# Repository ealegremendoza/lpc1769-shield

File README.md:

# PRYECTOR LPC1769-SHIELD
- La idea del mismo es poder conectarse rápidamente al lpcxpresso lpc1769.
- Proyecto creado en KICAD4.

### Todo listo para el planchado. 
- Ver en la carpeta pdf el archivo listo para planchar.

Alegre Ezequiel.

https://github.com/ealegremendoza

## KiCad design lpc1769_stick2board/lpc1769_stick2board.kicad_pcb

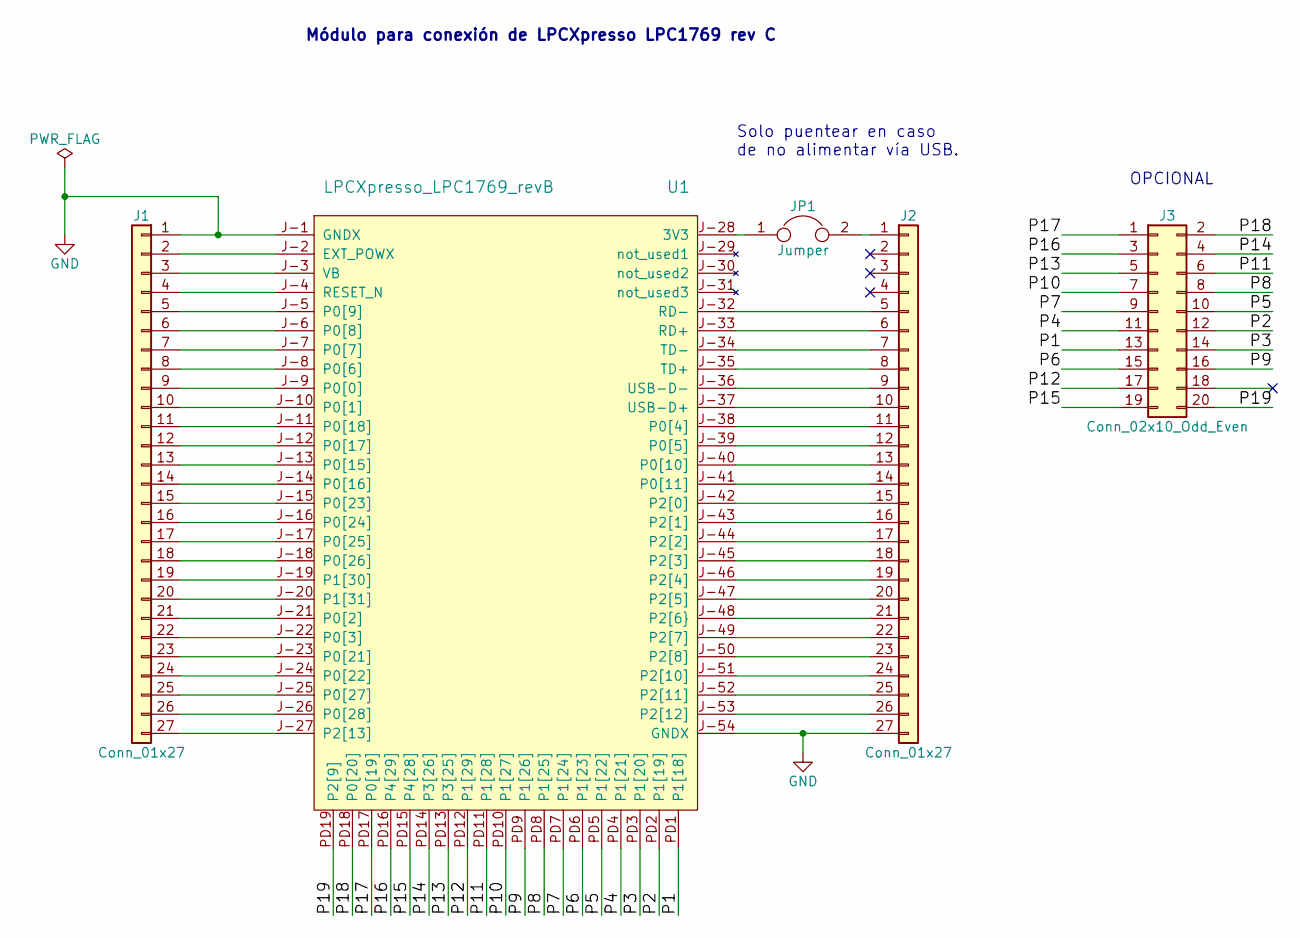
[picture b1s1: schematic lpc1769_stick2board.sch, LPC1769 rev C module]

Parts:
J1, J2: Conn_01x27; Socket_Strip_Straight_1x27_Pitch2.54mm
J3: Conn_02x10_Odd_Even; Socket_Strip_Straight_2x10_Pitch2.54mm
JP1: Jumper; Socket_Strip_Straight_1x02_Pitch2.54mm
U1: LPCXpresso_LPC1769_revB; lpc1769_board_revC

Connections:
/P1: J3.13, U1.PD1 (P1[18])
/P2: J3.12, U1.PD2 (P1[19])
/P3: J3.14, U1.PD3 (P1[20])
/P4: J3.11, U1.PD4 (P1[21])
/P5: J3.10, U1.PD5 (P1[22])
/P6: J3.15, U1.PD6 (P1[23])
/P7: J3.9, U1.PD7 (P1[24])
/P8: J3.8, U1.PD8 (P1[25])
/P9: J3.16, U1.PD9 (P1[26])
/P10: J3.7, U1.PD10 (P1[27])
/P11: J3.6, U1.PD11 (P1[28])
/P12: J3.17, U1.PD12 (P1[29])
/P13: J3.5, U1.PD13 (P3[25])
/P14: J3.4, U1.PD14 (P3[26])
/P15: J3.19, U1.PD15 (P4[28])
/P16: J3.3, U1.PD16 (P4[29])
/P17: J3.1, U1.PD17 (P0[19])
/P18: J3.2, U1.PD18 (P0[20])
/P19: J3.20, U1.PD19 (P2[9])
GND: J1.1, J2.27, U1.J-1 (GNDX), U1.J-54 (GNDX)
unnamed: J1.2, U1.J-2 (EXT_POWX)
unnamed: J1.3, U1.J-3 (VB)
unnamed: J1.4, U1.J-4 (RESET_N)
unnamed: J1.5, U1.J-5 (P0[9])
unnamed: J1.6, U1.J-6 (P0[8])
unnamed: J1.7, U1.J-7 (P0[7])
unnamed: J1.8, U1.J-8 (P0[6])
unnamed: J1.9, U1.J-9 (P0[0])
unnamed: J1.10, U1.J-10 (P0[1])
unnamed: J1.11, U1.J-11 (P0[18])
unnamed: J1.12, U1.J-12 (P0[17])
unnamed: J1.13, U1.J-13 (P0[15])
unnamed: J1.14, U1.J-14 (P0[16])
unnamed: J1.15, U1.J-15 (P0[23])
unnamed: J1.16, U1.J-16 (P0[24])
unnamed: J1.17, U1.J-17 (P0[25])
unnamed: J1.18, U1.J-18 (P0[26])
unnamed: J1.19, U1.J-19 (P1[30])
unnamed: J1.20, U1.J-20 (P1[31])
unnamed: J1.21, U1.J-21 (P0[2])
unnamed: J1.22, U1.J-22 (P0[3])
unnamed: J1.23, U1.J-23 (P0[21])
unnamed: J1.24, U1.J-24 (P0[22])
unnamed: J1.25, U1.J-25 (P0[27])
unnamed: J1.26, U1.J-26 (P0[28])
unnamed: J1.27, U1.J-27 (P2[13])
unnamed: J2.1, JP1.2
unnamed: J2.5, U1.J-32 (RD-)
unnamed: J2.6, U1.J-33 (RD+)
unnamed: J2.7, U1.J-34 (TD-)
unnamed: J2.8, U1.J-35 (TD+)
unnamed: J2.9, U1.J-36 (USB-D-)
unnamed: J2.10, U1.J-37 (USB-D+)
unnamed: J2.11, U1.J-38 (P0[4])
unnamed: J2.12, U1.J-39 (P0[5])
unnamed: J2.13, U1.J-40 (P0[10])
unnamed: J2.14, U1.J-41 (P0[11])
unnamed: J2.15, U1.J-42 (P2[0])
unnamed: J2.16, U1.J-43 (P2[1])
unnamed: J2.17, U1.J-44 (P2[2])
unnamed: J2.18, U1.J-45 (P2[3])
unnamed: J2.19, U1.J-46 (P2[4])
unnamed: J2.20, U1.J-47 (P2[5])
unnamed: J2.21, U1.J-48 (P2[6})
unnamed: J2.22, U1.J-49 (P2[7])
unnamed: J2.23, U1.J-50 (P2[8])
unnamed: J2.24, U1.J-51 (P2[10])
unnamed: J2.25, U1.J-52 (P2[11])
unnamed: J2.26, U1.J-53 (P2[12])
unnamed: JP1.1, U1.J-28 (3V3)

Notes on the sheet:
Módulo para conexión de LPCXpresso LPC1769 rev C
OPCIONAL
Solo puentear en caso de no alimentar vía USB.

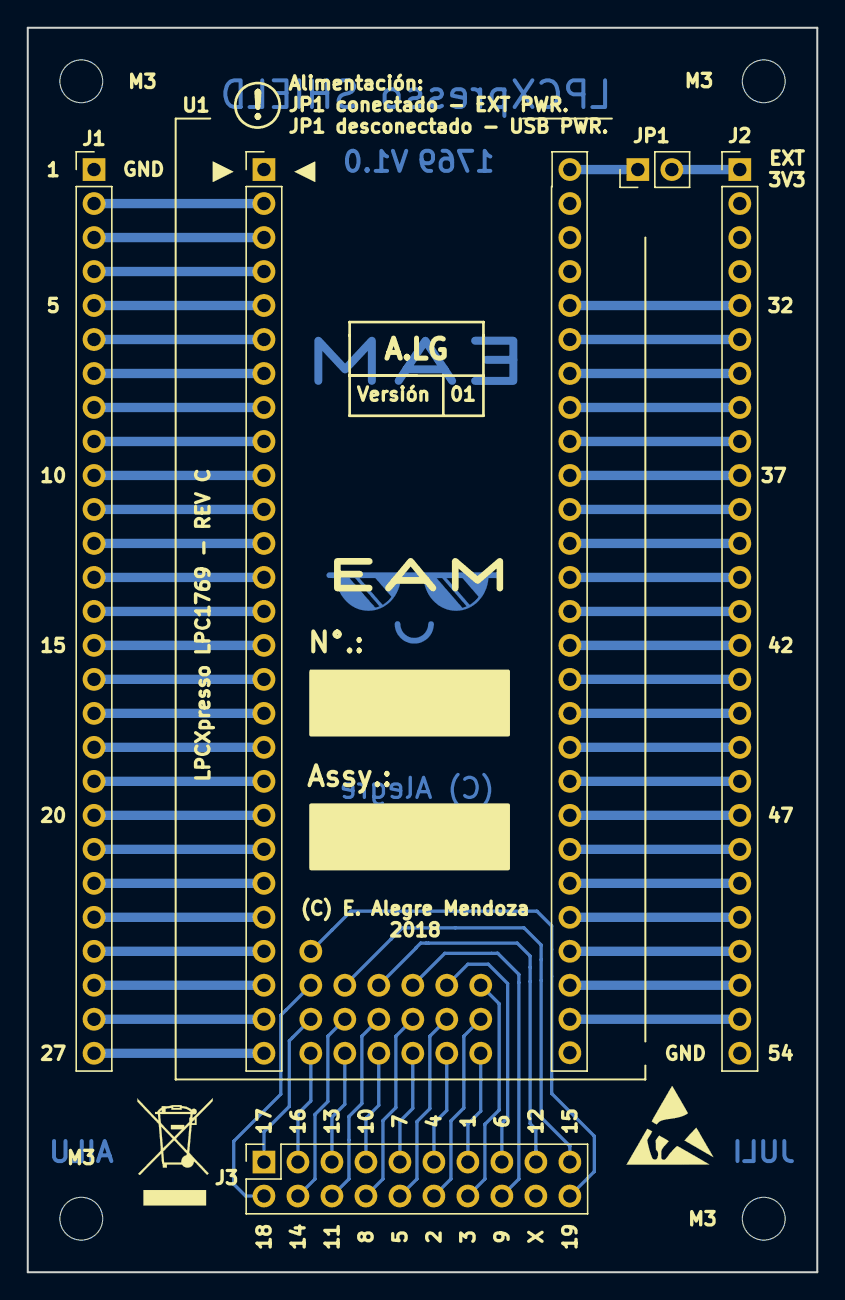
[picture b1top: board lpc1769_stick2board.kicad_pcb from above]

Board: 2 copper layers, 59.0 x 93.0 mm, 11 parts (0 on the bottom side), 70 nets.

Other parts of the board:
F1, F2: Fiducial_1mm_Dia_2.54mm_Outer_CopperBottom
M3, M3#2, M3#3, M3#4: MountingHole_3.2mm_M3

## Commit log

2018-10-17 init
2018-10-17 agregado proyecto kicad
2018-10-17 readme update
2018-10-21 fin pcb
2018-10-21 texto de prueba
2018-10-22 PLACA TERMINADA. LISTA PARA PLANCHAR
2018-10-22 agregada plantilla para planchar
